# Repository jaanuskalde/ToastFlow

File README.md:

ToastFlow
=========

Toaster reflow oven controller. Abandoned project due to some bugs and safety.

##Usage

Put boards with solder paste in the oven. Press the red button. When the led switches off you can take the boards out or something.

##About

Schematic is in KiCad. Schematic idea is from [ST app note "MICROCONTROLLER AND TRIACS ON THE 110/240V MAINS"](http://www.datasheetcatalog.org/datasheet/SGSThomsonMicroelectronics/mXxuyw.pdf). [Reflow profile](http://www.actel.com/documents/Solder_Reflow_LeadFree.pdf).

Uses weird temperature sensor. Heats boards to 150 degrees (1.3 kΩ, 3.143V, 41200), keeps there for 1m 10s and heats it up to 220 degrees (1.8 kΩ, 2.75V, 36000) 1m 30s.

| Part      | Value |Pack | Farnell Code  |
|-----------|-------|-----|-------|
|Attiny13   |       | SO8 |1704567|
|Temp sensor|       |DO-34|1672407|
|The button |||1634684|
|Screw terminal|3x3.5 mm||3882627|
|TRIAC|4A|DPAK|1757884|
|X1 capacitor|100 nF||1907253|
|Fuse|4A||1829558|
|Diode|||8150206|
|Reservoir capacitor|100 µF|5mm|9452354|
|Zener diode|5V1|SOD323|8735735|

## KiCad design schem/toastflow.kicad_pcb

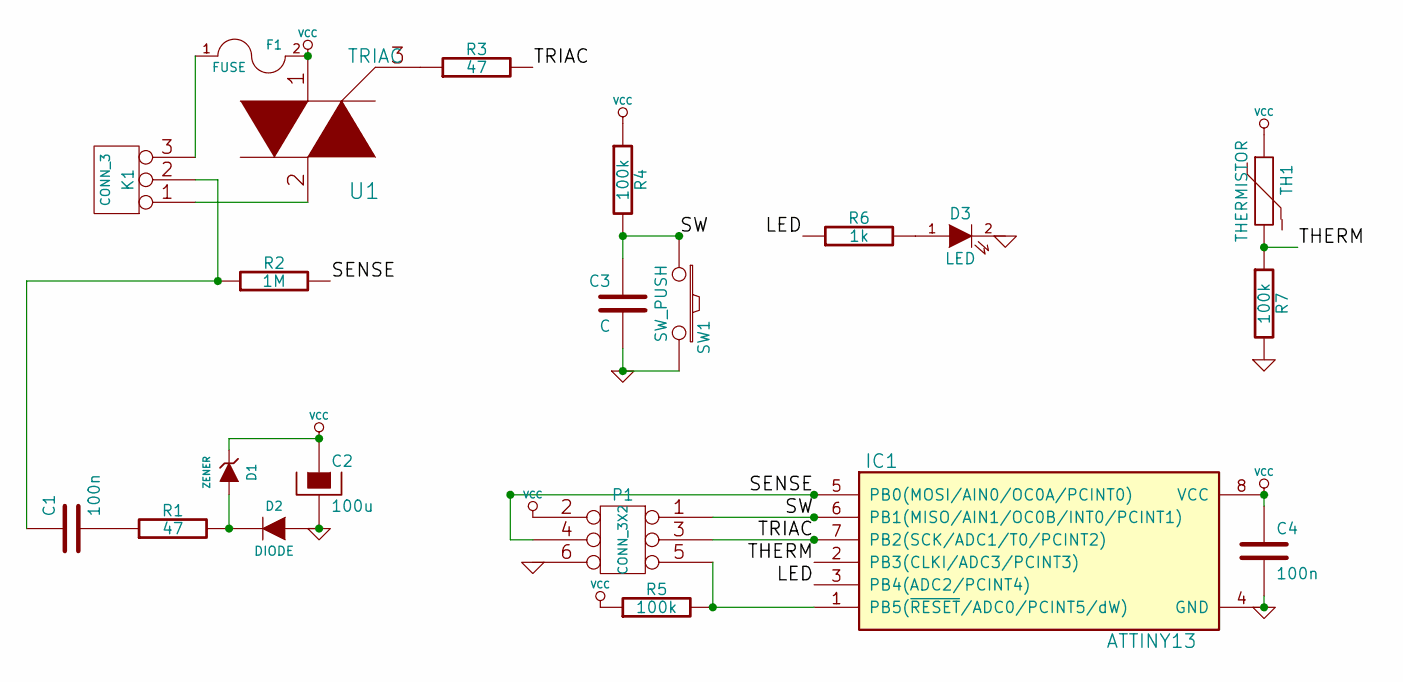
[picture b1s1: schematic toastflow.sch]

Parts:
C1, C4: 100n
C2: 100u
C3: C
D1: ZENER
D2: DIODE
D3: LED
F1: FUSE
IC1: ATTINY13; DIP8
K1: CONN_3
P1: CONN_3X2
R1, R3: 47
R2: 1M
R4, R5, R7: 100k
R6: 1k
SW1: SW_PUSH
TH1: THERMISTOR
U1: TRIAC

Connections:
/LED: IC1.3 (PB4(ADC2/PCINT4)), R6.1
/SENSE: IC1.5 (PB0(MOSI/AIN0/OC0A/PCINT0)), P1.4, R2.2
/SW: C3.1, IC1.6 (PB1(MISO/AIN1/OC0B/INT0/PCINT1)), P1.1, R4.2, SW1.1
/THERM: IC1.2 (PB3(CLKI/ADC3/PCINT3)), R7.1, TH1.2
/TRIAC: IC1.7 (PB2(SCK/ADC1/T0/PCINT2)), P1.3, R3.2
GND: C2.2, C3.2, C4.2, D2.2 (A), D3.2 (K), IC1.4 (GND), P1.6, R7.2, SW1.2
unnamed: D1.2 (A), D2.1 (K), R1.2
unnamed: C1.2, R1.1
unnamed: C1.1, K1.2 (PM), R2.1
unnamed: R3.1, U1.3
unnamed: K1.1, U1.2
unnamed: F1.1, K1.3
unnamed: D3.1 (A), R6.2
unnamed: IC1.1 (PB5(~RESET~/ADC0/PCINT5/dW)), P1.5, R5.2
VCC: C2.1, C4.1, D1.1 (K), F1.2, IC1.8 (VCC), P1.2, R4.1, R5.1, TH1.1, U1.1

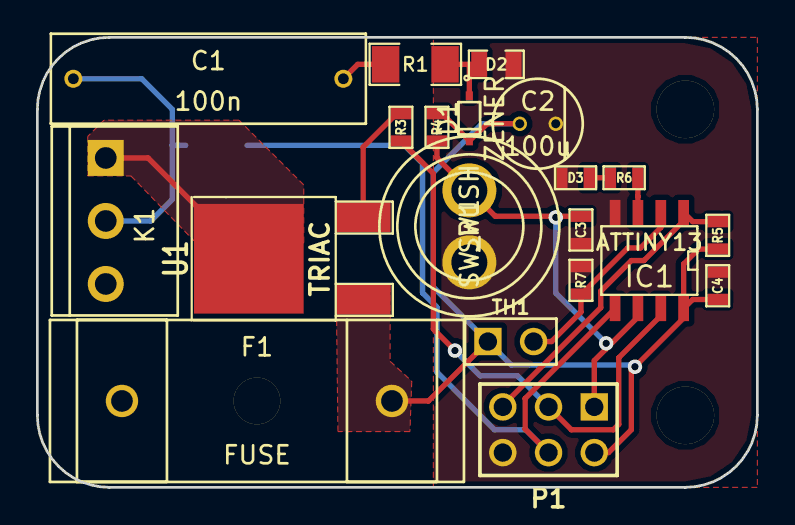
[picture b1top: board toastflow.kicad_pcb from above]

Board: 2 copper layers, 40.0 x 25.0 mm, 23 parts (1 on the bottom side), 15 nets.

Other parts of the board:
drill_3.2mm, drill_3.2mm#2: VAL**; drill_3.2mm

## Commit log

2013-02-18 Routed ver1 of PCB
2013-02-18 todo
2013-02-19 Blank code template added.
2013-02-20 Blank code
2013-02-20 Blanker code
2013-02-20 Fixed triac pin.
2013-02-20 IO, program, fix
2013-02-27 Working always on code
2013-02-27 Smth
2013-02-27 Final code before testing
2013-03-10 Real code, some bugs.
2013-03-10 Component fix
2013-07-08 Final commit
